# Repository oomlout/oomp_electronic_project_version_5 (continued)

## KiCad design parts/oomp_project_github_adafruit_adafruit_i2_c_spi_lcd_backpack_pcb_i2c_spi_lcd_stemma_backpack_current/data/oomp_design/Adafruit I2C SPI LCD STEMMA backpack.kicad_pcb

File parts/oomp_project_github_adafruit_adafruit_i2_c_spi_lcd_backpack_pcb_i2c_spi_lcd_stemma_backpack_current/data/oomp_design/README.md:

# OOMP KiCad design copy

Open `Adafruit I2C SPI LCD STEMMA backpack.kicad_pro` (or the `.kicad_pcb` / `.kicad_sch`) in KiCad. Local OOMP libraries are under `libraries/`. Original inputs are preserved in [../original/](../original/).

Only verified unchanged installed KiCad defaults were renamed. Modified, custom, unmatched and unavailable items remain unchanged. Soldering variants are never swapped during conversion. Existing pad coordinates, nets and UUIDs are preserved.

See [conversion_report.yaml](conversion_report.yaml) for every conversion and skip. Copy this directory before editing; regeneration refuses to overwrite edited design files.

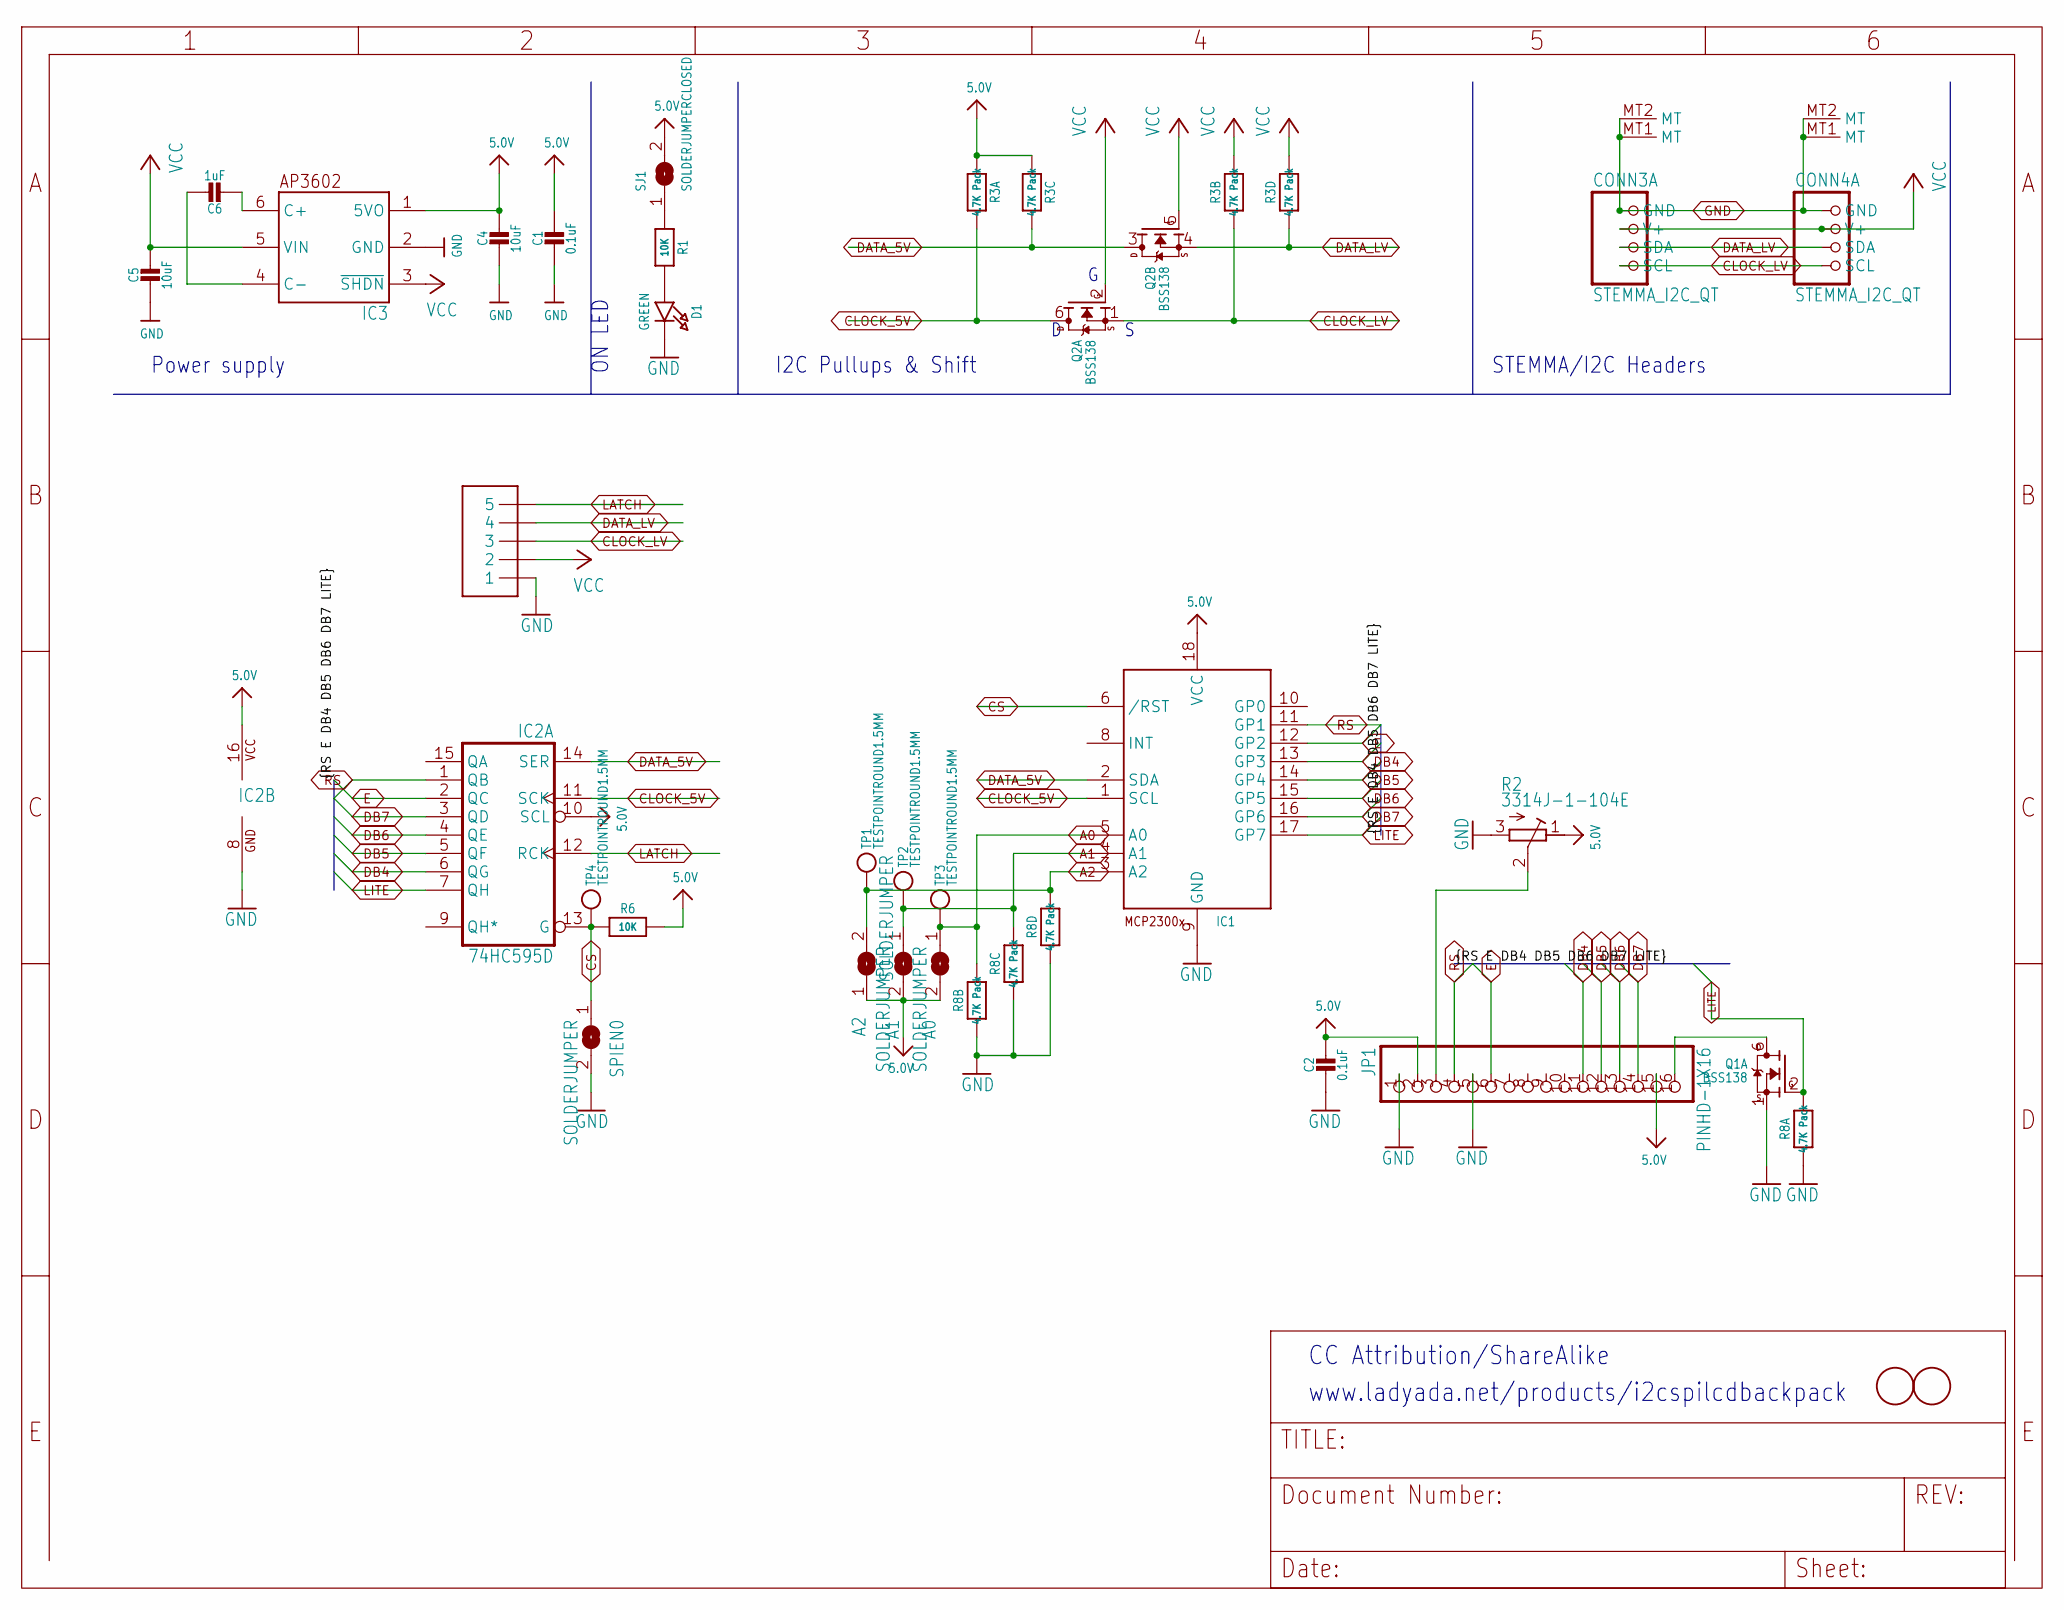
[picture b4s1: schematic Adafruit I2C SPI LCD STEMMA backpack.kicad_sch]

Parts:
A0, A1, A2: SOLDERJUMPER; SOLDERJUMPER_ARROW_NOPASTE
C1, C2: 0.1uF; 0603-NO
C4, C5: 10uF; 0805-NO
C6: 1uF; 0805-NO
CONN3, CONN4: STEMMA_I2C_QT; JST_SH4; LCSC C2845363
D1: GREEN; CHIPLED_0603_NOOUTLINE
IC1: MCP23008/SO; SO18W
IC2: 74HC595D; SO16
IC3: AP3602/RT9361; SOT23-6
J1: 1X5; 1X05-3.5MM
JP1: PINHD-1X16; 1X16
Q1, Q2: BSS138; SOT363; JLC_ROTATION 270
R1, R6: 10K; 0603-NO
R2: 3314J-1-104E; RTRIM3314J
R3, R8: 4.7K Pack; RESPACK_4X0603
SJ1: SOLDERJUMPERCLOSED; SOLDERJUMPER_CLOSEDWIRE
SPIEN0: SOLDERJUMPER; SOLDERJUMPER_ARROW_NOPASTE
TP1, TP2, TP3, TP4: TESTPOINTROUND1.5MM; TESTPOINT_ROUND_1.5MM
U$1, U$2: FIDUCIAL; FIDUCIAL_1MM

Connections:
5.0V: A0.2, A1.2, A2.1, C1.1, C2.1, C4.1, IC1.18 (VCC), IC2.10 (SCL), IC2.16 (VCC), IC3.1 (5VO), JP1.2, JP1.15, R2.1 (E), R3.1, R3.3 (1), R6.1, SJ1.2
A0: A0.1, IC1.5 (A0), R8.7 (2), TP3.P$1
A1: A1.1, IC1.4 (A1), R8.6 (2), TP2.P$1
A2: A2.2, IC1.3 (A2), R8.5 (2), TP1.P$1
CLOCK_5V: IC1.1 (SCL), IC2.11 (SCK), Q2.6 (D), R3.8 (2)
CLOCK_LV: CONN3.4 (SCL), CONN4.4 (SCL), J1.3, Q2.1 (S), R3.7 (2)
CONTRAST: JP1.3, R2.2 (S)
CS: IC1.6 (/RST), IC2.13 (G), R6.2, SPIEN0.1, TP4.P$1
DATA_5V: IC1.2 (SDA), IC2.14 (SER), Q2.3 (D), R3.6 (2)
DATA_LV: CONN3.3 (SDA), CONN4.3 (SDA), J1.4, Q2.4 (S), R3.5 (2)
DB4: IC1.13 (GP3), IC2.6 (QG), JP1.11
DB5: IC1.14 (GP4), IC2.5 (QF), JP1.12
DB6: IC1.15 (GP5), IC2.4 (QE), JP1.13
DB7: IC1.16 (GP6), IC2.3 (QD), JP1.14
E: IC1.12 (GP2), IC2.2 (QC), JP1.6
GND: C1.2, C2.2, C4.2, C5.2, CONN3.1 (GND), CONN3.MT1 (MT), CONN3.MT2 (MT), CONN4.1 (GND), CONN4.MT1 (MT), CONN4.MT2 (MT), D1.C, IC1.9 (GND), IC2.8 (GND), IC3.2 (GND), J1.1, JP1.1, JP1.5, Q1.1 (S), R2.3 (A), R8.1, R8.2 (1), R8.3 (1), R8.4 (1), SPIEN0.2
LATCH: IC2.12 (RCK), J1.5
LEDK: JP1.16, Q1.6 (D)
LITE: IC1.17 (GP7), IC2.7 (QH), Q1.2 (G), R8.8 (2)
unnamed: D1.A, R1.2
unnamed: R1.1, SJ1.1
unnamed: C6.2, IC3.6 (C+)
unnamed: C6.1, IC3.4 (C-)
RS: IC1.11 (GP1), IC2.1 (QB), JP1.4
VCC: C5.1, CONN3.2 (V+), CONN4.2 (V+), IC3.3 (~SHDN), IC3.5 (VIN), J1.2, Q2.2 (G), Q2.5 (G), R3.2 (1), R3.4 (1)

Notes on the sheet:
I2C Pullups & Shift
Power supply
CC Attribution/ShareAlike
www.ladyada.net/products/i2cspilcdbackpack
STEMMA/I2C Headers
ON LED

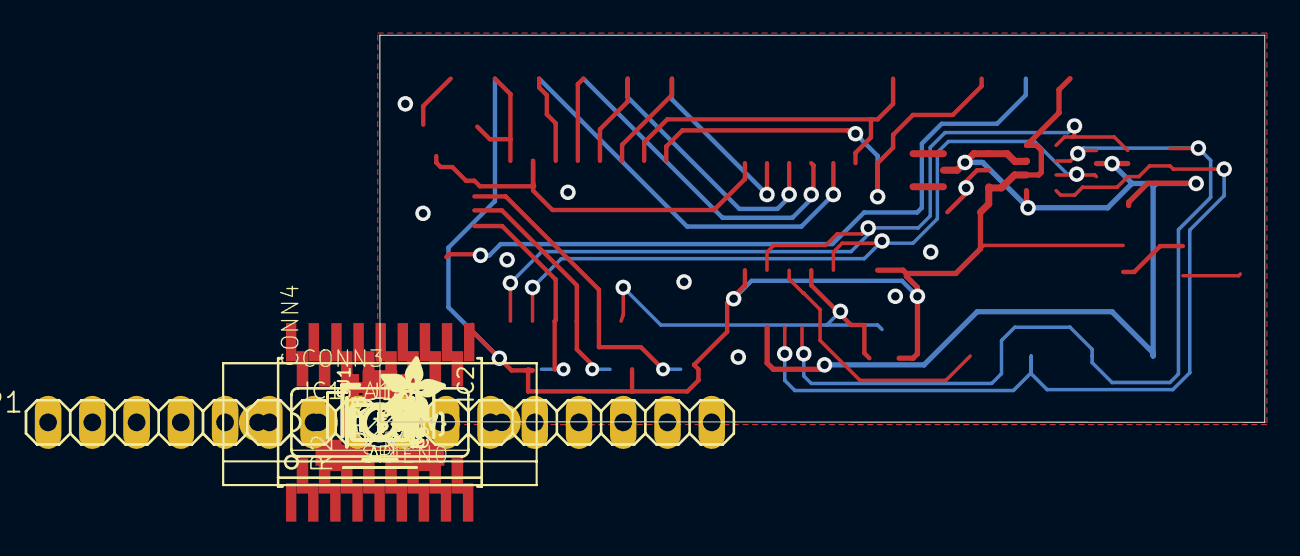
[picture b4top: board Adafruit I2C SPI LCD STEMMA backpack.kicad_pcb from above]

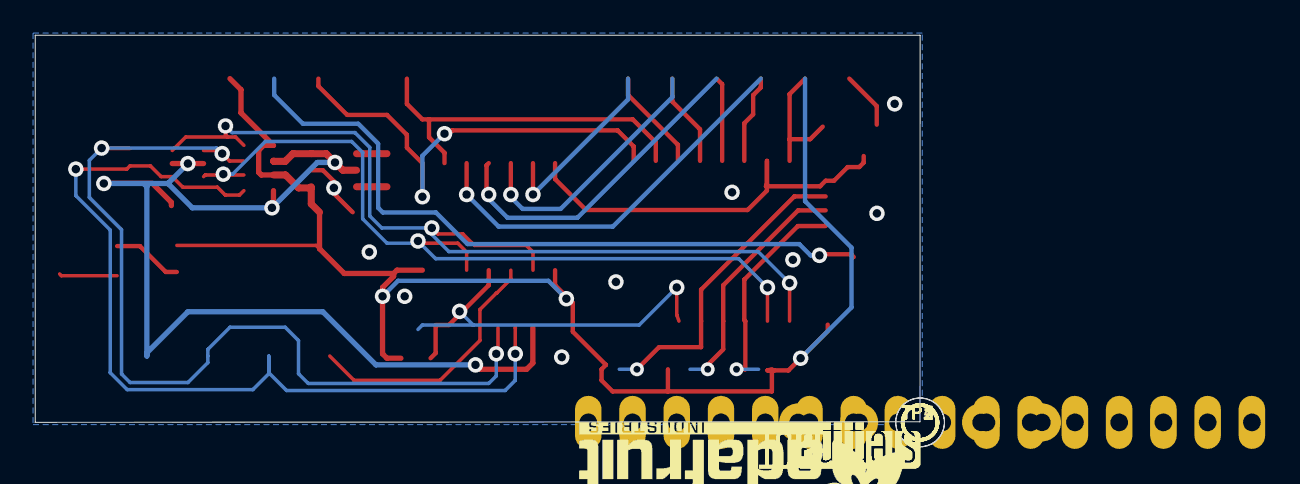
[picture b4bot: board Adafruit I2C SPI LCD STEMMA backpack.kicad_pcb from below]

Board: 16 copper layers, 50.8 x 22.2 mm, 51 parts (8 on the bottom side), 25 nets.

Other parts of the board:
PLABEL0: PLABEL0
PLABEL1: PLABEL1
PLABEL2: PLABEL2
PLABEL3: PLABEL3
PLABEL4: PLABEL4
PLABEL5: PLABEL5
PLABEL6: PLABEL6
PLABEL7: PLABEL7
PLABEL8: PLABEL8
PLABEL9: PLABEL9
PLABEL10: PLABEL10
PLABEL11: PLABEL11
PLABEL12: PLABEL12
U$4: ADAFRUIT_3.5MM
U$7: PCBFEAT-REV-040
U$11, U$12: STEMMAQT
U$23: ADAFRUIT_TEXT_20MM
UNK_HOLE_0: dummyfp0
UNK_HOLE_1: dummyfp1

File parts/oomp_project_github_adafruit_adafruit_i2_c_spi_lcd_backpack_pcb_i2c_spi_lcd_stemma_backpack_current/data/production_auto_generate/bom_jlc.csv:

Comment,Designator,Footprint,LCSC Part #
,JP1,Adafruit I2C SPI LCD STEMMA backpack-import-fps:1X16,C7501270
,U$4,Adafruit I2C SPI LCD STEMMA backpack-import-fps:ADAFRUIT_3.5MM,
,U$23,Adafruit I2C SPI LCD STEMMA backpack-import-fps:ADAFRUIT_TEXT_20MM,
,U$7,Adafruit I2C SPI LCD STEMMA backpack-import-fps:PCBFEAT-REV-040,
,PLABEL0,Adafruit I2C SPI LCD STEMMA backpack-import-fps:PLABEL0,
,PLABEL1,Adafruit I2C SPI LCD STEMMA backpack-import-fps:PLABEL1,
,PLABEL10,Adafruit I2C SPI LCD STEMMA backpack-import-fps:PLABEL10,
,PLABEL11,Adafruit I2C SPI LCD STEMMA backpack-import-fps:PLABEL11,
,PLABEL12,Adafruit I2C SPI LCD STEMMA backpack-import-fps:PLABEL12,
,PLABEL2,Adafruit I2C SPI LCD STEMMA backpack-import-fps:PLABEL2,
,PLABEL3,Adafruit I2C SPI LCD STEMMA backpack-import-fps:PLABEL3,
,PLABEL4,Adafruit I2C SPI LCD STEMMA backpack-import-fps:PLABEL4,
,PLABEL5,Adafruit I2C SPI LCD STEMMA backpack-import-fps:PLABEL5,
,PLABEL6,Adafruit I2C SPI LCD STEMMA backpack-import-fps:PLABEL6,
,PLABEL7,Adafruit I2C SPI LCD STEMMA backpack-import-fps:PLABEL7,
,PLABEL8,Adafruit I2C SPI LCD STEMMA backpack-import-fps:PLABEL8,
,PLABEL9,Adafruit I2C SPI LCD STEMMA backpack-import-fps:PLABEL9,
,"A0,A1,A2,SPIEN0",Adafruit I2C SPI LCD STEMMA backpack-import-fps:SOLDERJUMPER_ARROW_NOPASTE,
,"U$11,U$12",Adafruit I2C SPI LCD STEMMA backpack-import-fps:STEMMAQT,
,"TP1,TP2,TP3,TP4",Adafruit I2C SPI LCD STEMMA backpack-import-fps:TESTPOINT_ROUND_1.5MM,
0.1uF,"C1,C2",Adafruit I2C SPI LCD STEMMA backpack-import-fps:0603-NO,C14663
10K,"R1,R6",Adafruit I2C SPI LCD STEMMA backpack-import-fps:0603-NO,C98220
10uF,"C4,C5",Adafruit I2C SPI LCD STEMMA backpack-import-fps:0805-NO,
1uF,C6,Adafruit I2C SPI LCD STEMMA backpack-import-fps:0805-NO,
1X5,J1,Adafruit I2C SPI LCD STEMMA backpack-import-fps:1X05-3.5MM,C42431835
3314J-1-104E,R2,Adafruit I2C SPI LCD STEMMA backpack-import-fps:RTRIM3314J,
4.7K Pack,"R3,R8",Adafruit I2C SPI LCD STEMMA backpack-import-fps:RESPACK_4X0603,C23162
74HC595D,IC2,Adafruit I2C SPI LCD STEMMA backpack-import-fps:SO16,
AP3602/RT9361,IC3,Adafruit I2C SPI LCD STEMMA backpack-import-fps:SOT23-6,
BSS138,"Q1,Q2",Adafruit I2C SPI LCD STEMMA backpack-import-fps:SOT363,
FIDUCIAL,"U$1,U$2",Adafruit I2C SPI LCD STEMMA backpack-import-fps:FIDUCIAL_1MM,
GREEN,D1,Adafruit I2C SPI LCD STEMMA backpack-import-fps:CHIPLED_0603_NOOUTLINE,
MCP23008/SO,IC1,Adafruit I2C SPI LCD STEMMA backpack-import-fps:SO18W,
STEMMA_I2C_QT,"CONN3,CONN4",Adafruit I2C SPI LCD STEMMA backpack-import-fps:JST_SH4,C160404

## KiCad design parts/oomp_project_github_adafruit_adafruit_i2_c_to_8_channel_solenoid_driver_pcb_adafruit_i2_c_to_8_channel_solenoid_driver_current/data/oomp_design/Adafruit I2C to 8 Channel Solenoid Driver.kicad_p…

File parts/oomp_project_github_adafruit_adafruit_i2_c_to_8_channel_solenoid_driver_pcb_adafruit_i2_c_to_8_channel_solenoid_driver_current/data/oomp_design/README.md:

# OOMP KiCad design copy

Open `Adafruit I2C to 8 Channel Solenoid Driver.kicad_pro` (or the `.kicad_pcb` / `.kicad_sch`) in KiCad. Local OOMP libraries are under `libraries/`. Original inputs are preserved in [../original/](../original/).

Only verified unchanged installed KiCad defaults were renamed. Modified, custom, unmatched and unavailable items remain unchanged. Soldering variants are never swapped during conversion. Existing pad coordinates, nets and UUIDs are preserved.

See [conversion_report.yaml](conversion_report.yaml) for every conversion and skip. Copy this directory before editing; regeneration refuses to overwrite edited design files.

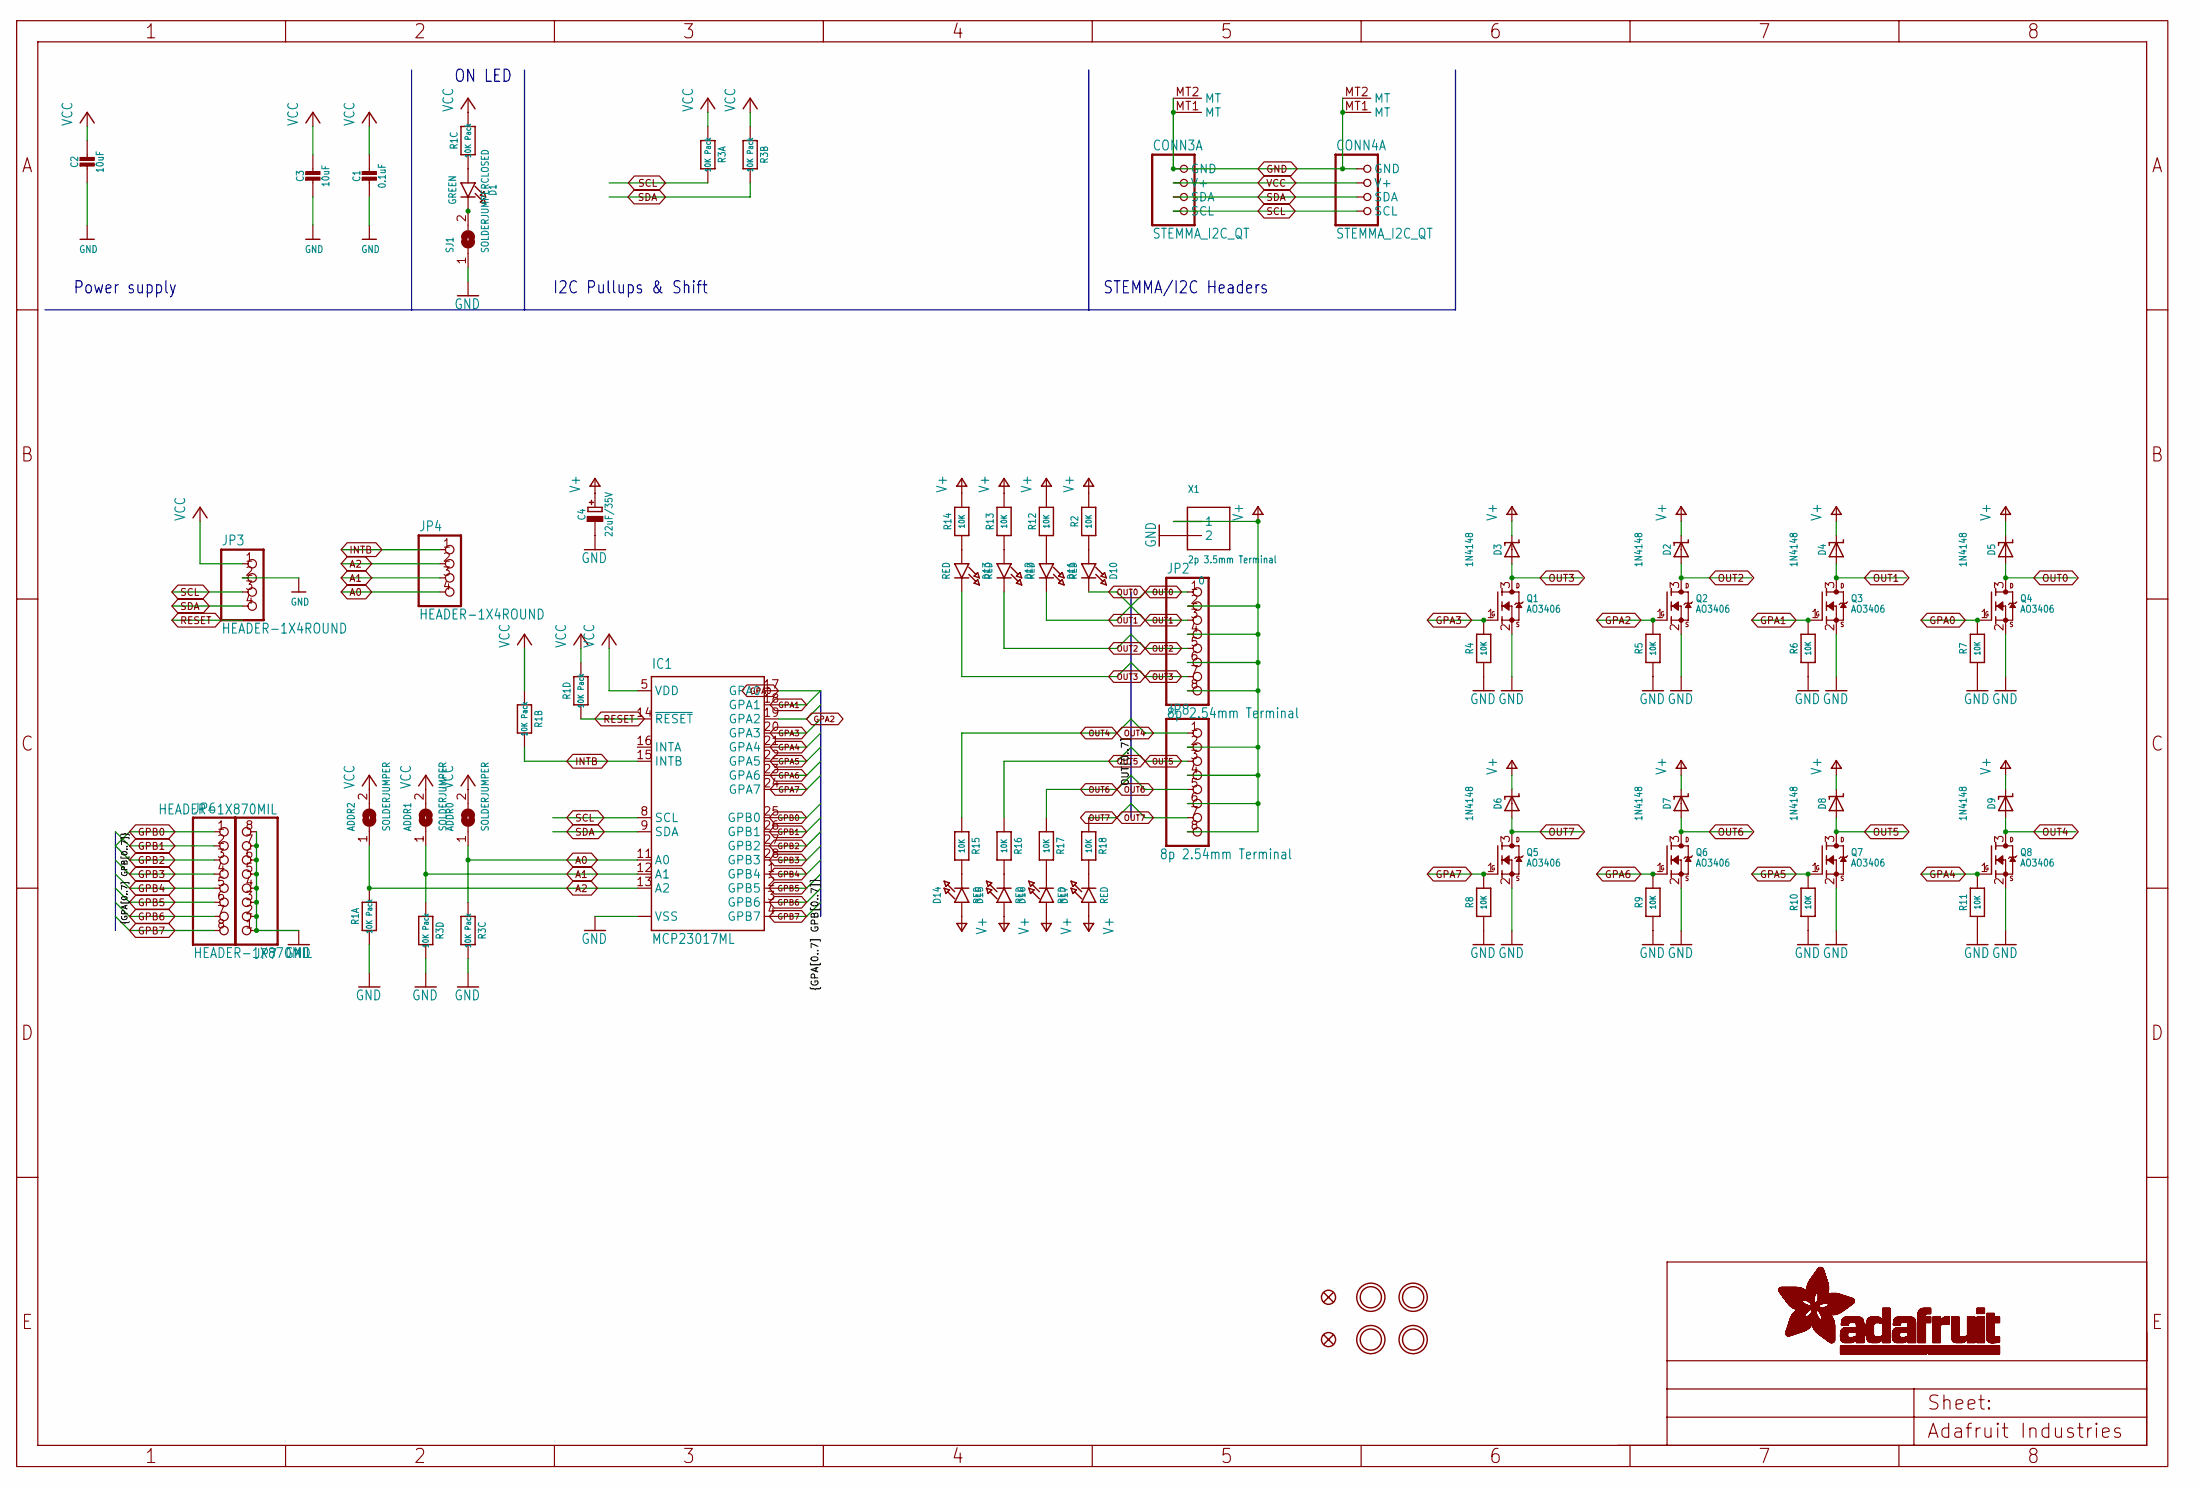
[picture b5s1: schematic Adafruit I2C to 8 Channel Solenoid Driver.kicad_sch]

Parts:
ADDR0, ADDR1, ADDR2: SOLDERJUMPER; SOLDERJUMPER_ARROW_NOPASTE
C1: 0.1uF; 0603-NO
C2, C3: 10uF; 0805-NO
C4: 22uF/35V; PANASONIC_C
CONN3, CONN4: STEMMA_I2C_QT; JST_SH4; LCSC C2845363
D1: GREEN; CHIPLED_0603_NOOUTLINE
D2, D3, D4, D5, D6, D7, D8, D9: 1N4148; SOD-323
D10, D11, D12, D13, D14, D15, D16, D17: RED; CHIPLED_0603_NOOUTLINE
FID3, FID4: FIDUCIAL_1MM
IC1: MCP23017ML; QFN28-ML_6X6MM; MPN MCP23017-E/ML
JP2, JP8: 8p 2.54mm Terminal; 1X08_2.54MMTERMINAL
JP3, JP4: HEADER-1X4ROUND; 1X04_ROUND
JP6, JP7: HEADER-1X870MIL; 1X08_ROUND_70
Q1, Q2, Q3, Q4, Q5, Q6, Q7, Q8: AO3406; SOT23-WIDE
R1, R3: 10K Pack; RESPACK_4X0603
R2, R4, R5, R6, R7, R8, R9, R10, R11, R12, R13, R14, R15, R16, R17, R18: 10K; 0603-NO
SJ1: SOLDERJUMPERCLOSED; SOLDERJUMPER_CLOSEDWIRE
U$1, U$17, U$19, U$21: MOUNTINGHOLE2.5; MOUNTINGHOLE_2.5_PLATED
X1: 2p 3.5mm Terminal; TERMBLOCK_1X2-3.5MM

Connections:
A0: ADDR0.1, IC1.11 (A0), JP4.4, R3.3 (1)
A1: ADDR1.1, IC1.12 (A1), JP4.3, R3.4 (1)
A2: ADDR2.1, IC1.13 (A2), JP4.2, R1.8 (2)
GND: C1.2, C2.2, C3.2, C4.-, CONN3.1 (GND), CONN3.MT1 (MT), CONN3.MT2 (MT), CONN4.1 (GND), CONN4.MT1 (MT), CONN4.MT2 (MT), IC1.6 (VSS), IC1.EXP (VSS), JP3.2, JP7.1, JP7.2, JP7.3, JP7.4, JP7.5, JP7.6, JP7.7, JP7.8, Q1.2 (S), Q2.2 (S), Q3.2 (S), Q4.2 (S), Q5.2 (S), Q6.2 (S), Q7.2 (S), Q8.2 (S), R1.1, R3.5 (2), R3.6 (2), R4.1, R5.1, R6.1, R7.1, R8.1, R9.1, R10.1, R11.1, SJ1.1, X1.2
GPA0: IC1.17 (GPA0), Q4.1 (G), R7.2
GPA1: IC1.18 (GPA1), Q3.1 (G), R6.2
GPA2: IC1.19 (GPA2), Q2.1 (G), R5.2
GPA3: IC1.20 (GPA3), Q1.1 (G), R4.2
GPA4: IC1.21 (GPA4), Q8.1 (G), R11.2
GPA5: IC1.22 (GPA5), Q7.1 (G), R10.2
GPA6: IC1.23 (GPA6), Q6.1 (G), R9.2
GPA7: IC1.24 (GPA7), Q5.1 (G), R8.2
GPB0: IC1.25 (GPB0), JP6.1
GPB1: IC1.26 (GPB1), JP6.2
GPB2: IC1.27 (GPB2), JP6.3
GPB3: IC1.28 (GPB3), JP6.4
GPB4: IC1.1 (GPB4), JP6.5
GPB5: IC1.2 (GPB5), JP6.6
GPB6: IC1.3 (GPB6), JP6.7
GPB7: IC1.4 (GPB7), JP6.8
INTB: IC1.15 (INTB), JP4.1, R1.7 (2)
unnamed: D1.A, R1.3 (1)
unnamed: D1.C, SJ1.2
unnamed: D10.A, R2.1
unnamed: D11.A, R12.1
unnamed: D12.A, R13.1
unnamed: D13.A, R14.1
unnamed: D14.C, R15.2
unnamed: D15.C, R16.2
unnamed: D16.C, R17.2
unnamed: D17.C, R18.2
OUT0: D5.A, D10.C, JP2.1, Q4.3 (D)
OUT1: D4.A, D11.C, JP2.3, Q3.3 (D)
OUT2: D2.A, D12.C, JP2.5, Q2.3 (D)
OUT3: D3.A, D13.C, JP2.7, Q1.3 (D)
OUT4: D9.A, JP8.1, Q8.3 (D), R15.1
OUT5: D8.A, JP8.3, Q7.3 (D), R16.1
OUT6: D7.A, JP8.5, Q6.3 (D), R17.1
OUT7: D6.A, JP8.7, Q5.3 (D), R18.1
RESET: IC1.14 (~RESET), R1.4 (1)
SCL: CONN3.4 (SCL), CONN4.4 (SCL), IC1.8 (SCL), JP3.3, R3.8 (2)
SDA: CONN3.3 (SDA), CONN4.3 (SDA), IC1.9 (SDA), JP3.4, R3.7 (2)
V+: C4.+, D2.C, D3.C, D4.C, D5.C, D6.C, D7.C, D8.C, D9.C, D14.A, D15.A, D16.A, D17.A, JP2.2, JP2.4, JP2.6, JP2.8, JP8.2, JP8.4, JP8.6, JP8.8, R2.2, R12.2, R13.2, R14.2, X1.1
VCC: ADDR0.2, ADDR1.2, ADDR2.2, C1.1, C2.1, C3.1, CONN3.2 (V+), CONN4.2 (V+), IC1.5 (VDD), JP3.1, R1.2 (1), R1.5 (2), R1.6 (2), R3.1, R3.2 (1)

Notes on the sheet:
STEMMA/I2C Headers
ON LED
I2C Pullups & Shift
Power supply

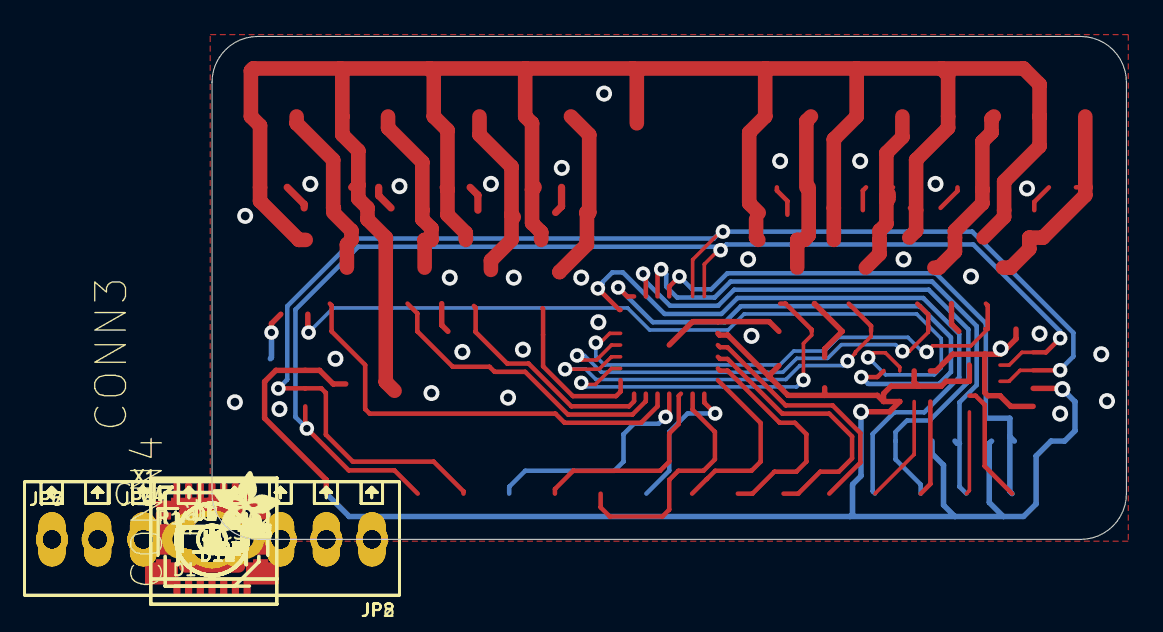
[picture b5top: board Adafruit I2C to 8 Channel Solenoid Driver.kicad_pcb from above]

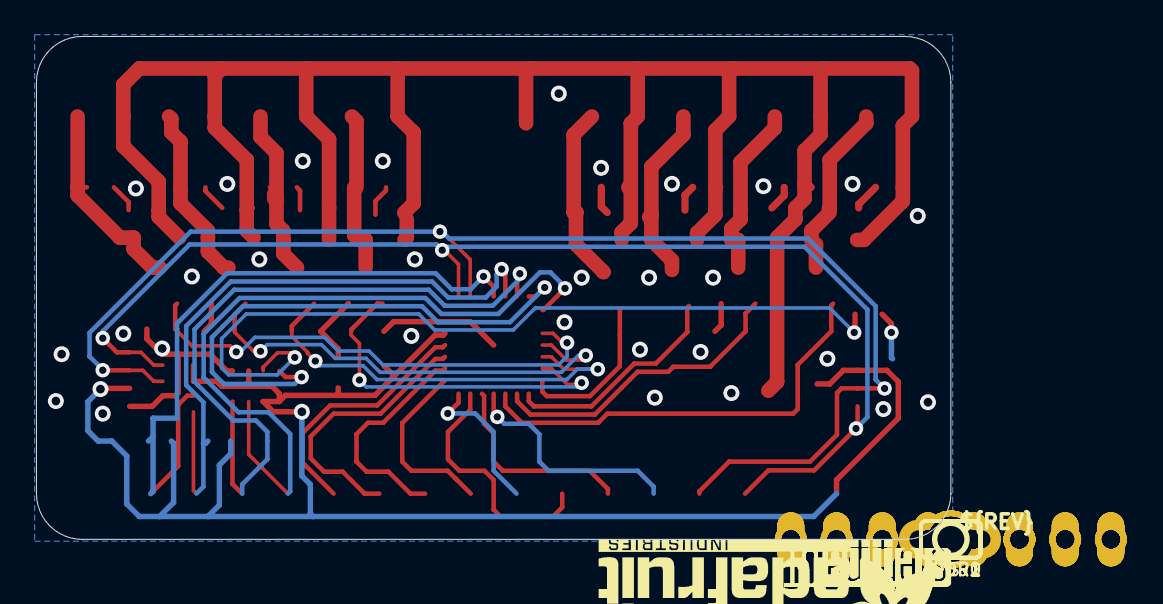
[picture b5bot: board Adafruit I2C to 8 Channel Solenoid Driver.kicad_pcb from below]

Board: 2 copper layers, 50.8 x 27.9 mm, 135 parts (32 on the bottom side), 44 nets.

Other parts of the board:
PLABEL0: PLABEL0
PLABEL1: PLABEL1
PLABEL2: PLABEL2
PLABEL3: PLABEL3
PLABEL4: PLABEL4
PLABEL5: PLABEL5
PLABEL6: PLABEL6
PLABEL7: PLABEL7
PLABEL8: PLABEL8
PLABEL9: PLABEL9
PLABEL10: PLABEL10
PLABEL11: PLABEL11
PLABEL12: PLABEL12
PLABEL13: PLABEL13
PLABEL14: PLABEL14
PLABEL15: PLABEL15
PLABEL16: PLABEL16
PLABEL17: PLABEL17
PLABEL18: PLABEL18
PLABEL19: PLABEL19
PLABEL20: PLABEL20
PLABEL21: PLABEL21
PLABEL22: PLABEL22
PLABEL23: PLABEL23
PLABEL24: PLABEL24
PLABEL25: PLABEL25
PLABEL26: PLABEL26
PLABEL27: PLABEL27
PLABEL28: PLABEL28
PLABEL29: PLABEL29
PLABEL30: PLABEL30
PLABEL31: PLABEL31
PLABEL32: PLABEL32
PLABEL33: PLABEL33
PLABEL34: PLABEL34
PLABEL35: PLABEL35
PLABEL36: PLABEL36
PLABEL37: PLABEL37
PLABEL38: PLABEL38
PLABEL39: PLABEL39
PLABEL40: PLABEL40
PLABEL41: PLABEL41
PLABEL42: PLABEL42
PLABEL43: PLABEL43
PLABEL44: PLABEL44
PLABEL45: PLABEL45
PLABEL46: PLABEL46
PLABEL47: PLABEL47
PLABEL48: PLABEL48
PLABEL49: PLABEL49
PLABEL50: PLABEL50
PLABEL51: PLABEL51
PLABEL52: PLABEL52
PLABEL53: PLABEL53
PLABEL54: PLABEL54
PLABEL55: PLABEL55
PLABEL56: PLABEL56
PLABEL57: PLABEL57
PLABEL58: PLABEL58
PLABEL59: PLABEL59
PLABEL60: PLABEL60
U$2: PLUS; SYMBOL_PLUS
U$3: SYMBOL_MINUS
U$4: ADAFRUIT_3.5MM
U$7: ADAFRUIT_TEXT_20MM
U$25: PCBFEAT-REV-040
U$30, U$31: STEMMAQT

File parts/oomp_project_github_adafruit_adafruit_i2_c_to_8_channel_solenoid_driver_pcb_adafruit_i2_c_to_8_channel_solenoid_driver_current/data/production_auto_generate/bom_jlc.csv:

Comment,Designator,Footprint,LCSC Part #
,"JP3,JP4",Adafruit I2C to 8 Channel Solenoid Driver-import-fps:1X04_ROUND,C42431795
,"JP6,JP7",Adafruit I2C to 8 Channel Solenoid Driver-import-fps:1X08_ROUND_70,C492421
,U$4,Adafruit I2C to 8 Channel Solenoid Driver-import-fps:ADAFRUIT_3.5MM,
,U$7,Adafruit I2C to 8 Channel Solenoid Driver-import-fps:ADAFRUIT_TEXT_20MM,
,U$25,Adafruit I2C to 8 Channel Solenoid Driver-import-fps:PCBFEAT-REV-040,
,PLABEL0,Adafruit I2C to 8 Channel Solenoid Driver-import-fps:PLABEL0,
,PLABEL1,Adafruit I2C to 8 Channel Solenoid Driver-import-fps:PLABEL1,
,PLABEL10,Adafruit I2C to 8 Channel Solenoid Driver-import-fps:PLABEL10,
,PLABEL11,Adafruit I2C to 8 Channel Solenoid Driver-import-fps:PLABEL11,
,PLABEL12,Adafruit I2C to 8 Channel Solenoid Driver-import-fps:PLABEL12,
,PLABEL13,Adafruit I2C to 8 Channel Solenoid Driver-import-fps:PLABEL13,
,PLABEL14,Adafruit I2C to 8 Channel Solenoid Driver-import-fps:PLABEL14,
,PLABEL15,Adafruit I2C to 8 Channel Solenoid Driver-import-fps:PLABEL15,
,PLABEL16,Adafruit I2C to 8 Channel Solenoid Driver-import-fps:PLABEL16,
,PLABEL17,Adafruit I2C to 8 Channel Solenoid Driver-import-fps:PLABEL17,
,PLABEL18,Adafruit I2C to 8 Channel Solenoid Driver-import-fps:PLABEL18,
,PLABEL19,Adafruit I2C to 8 Channel Solenoid Driver-import-fps:PLABEL19,
,PLABEL2,Adafruit I2C to 8 Channel Solenoid Driver-import-fps:PLABEL2,
,PLABEL20,Adafruit I2C to 8 Channel Solenoid Driver-import-fps:PLABEL20,
,PLABEL21,Adafruit I2C to 8 Channel Solenoid Driver-import-fps:PLABEL21,
,PLABEL22,Adafruit I2C to 8 Channel Solenoid Driver-import-fps:PLABEL22,
,PLABEL23,Adafruit I2C to 8 Channel Solenoid Driver-import-fps:PLABEL23,
,PLABEL24,Adafruit I2C to 8 Channel Solenoid Driver-import-fps:PLABEL24,
,PLABEL25,Adafruit I2C to 8 Channel Solenoid Driver-import-fps:PLABEL25,
,PLABEL26,Adafruit I2C to 8 Channel Solenoid Driver-import-fps:PLABEL26,
,PLABEL27,Adafruit I2C to 8 Channel Solenoid Driver-import-fps:PLABEL27,
,PLABEL28,Adafruit I2C to 8 Channel Solenoid Driver-import-fps:PLABEL28,
,PLABEL29,Adafruit I2C to 8 Channel Solenoid Driver-import-fps:PLABEL29,
,PLABEL3,Adafruit I2C to 8 Channel Solenoid Driver-import-fps:PLABEL3,
,PLABEL30,Adafruit I2C to 8 Channel Solenoid Driver-import-fps:PLABEL30,
,PLABEL31,Adafruit I2C to 8 Channel Solenoid Driver-import-fps:PLABEL31,
,PLABEL32,Adafruit I2C to 8 Channel Solenoid Driver-import-fps:PLABEL32,
,PLABEL33,Adafruit I2C to 8 Channel Solenoid Driver-import-fps:PLABEL33,
,PLABEL34,Adafruit I2C to 8 Channel Solenoid Driver-import-fps:PLABEL34,
,PLABEL35,Adafruit I2C to 8 Channel Solenoid Driver-import-fps:PLABEL35,
,PLABEL36,Adafruit I2C to 8 Channel Solenoid Driver-import-fps:PLABEL36,
,PLABEL37,Adafruit I2C to 8 Channel Solenoid Driver-import-fps:PLABEL37,
,PLABEL38,Adafruit I2C to 8 Channel Solenoid Driver-import-fps:PLABEL38,
,PLABEL39,Adafruit I2C to 8 Channel Solenoid Driver-import-fps:PLABEL39,
,PLABEL4,Adafruit I2C to 8 Channel Solenoid Driver-import-fps:PLABEL4,
,PLABEL40,Adafruit I2C to 8 Channel Solenoid Driver-import-fps:PLABEL40,
,PLABEL41,Adafruit I2C to 8 Channel Solenoid Driver-import-fps:PLABEL41,
,PLABEL42,Adafruit I2C to 8 Channel Solenoid Driver-import-fps:PLABEL42,
,PLABEL43,Adafruit I2C to 8 Channel Solenoid Driver-import-fps:PLABEL43,
,PLABEL44,Adafruit I2C to 8 Channel Solenoid Driver-import-fps:PLABEL44,
,PLABEL45,Adafruit I2C to 8 Channel Solenoid Driver-import-fps:PLABEL45,
,PLABEL46,Adafruit I2C to 8 Channel Solenoid Driver-import-fps:PLABEL46,
,PLABEL47,Adafruit I2C to 8 Channel Solenoid Driver-import-fps:PLABEL47,
,PLABEL48,Adafruit I2C to 8 Channel Solenoid Driver-import-fps:PLABEL48,
,PLABEL49,Adafruit I2C to 8 Channel Solenoid Driver-import-fps:PLABEL49,
,PLABEL5,Adafruit I2C to 8 Channel Solenoid Driver-import-fps:PLABEL5,
,PLABEL50,Adafruit I2C to 8 Channel Solenoid Driver-import-fps:PLABEL50,
,PLABEL51,Adafruit I2C to 8 Channel Solenoid Driver-import-fps:PLABEL51,
,PLABEL52,Adafruit I2C to 8 Channel Solenoid Driver-import-fps:PLABEL52,
,PLABEL53,Adafruit I2C to 8 Channel Solenoid Driver-import-fps:PLABEL53,
,PLABEL54,Adafruit I2C to 8 Channel Solenoid Driver-import-fps:PLABEL54,
,PLABEL55,Adafruit I2C to 8 Channel Solenoid Driver-import-fps:PLABEL55,
,PLABEL56,Adafruit I2C to 8 Channel Solenoid Driver-import-fps:PLABEL56,
,PLABEL57,Adafruit I2C to 8 Channel Solenoid Driver-import-fps:PLABEL57,
,PLABEL58,Adafruit I2C to 8 Channel Solenoid Driver-import-fps:PLABEL58,
,PLABEL59,Adafruit I2C to 8 Channel Solenoid Driver-import-fps:PLABEL59,
,PLABEL6,Adafruit I2C to 8 Channel Solenoid Driver-import-fps:PLABEL6,
,PLABEL60,Adafruit I2C to 8 Channel Solenoid Driver-import-fps:PLABEL60,
,PLABEL7,Adafruit I2C to 8 Channel Solenoid Driver-import-fps:PLABEL7,
,PLABEL8,Adafruit I2C to 8 Channel Solenoid Driver-import-fps:PLABEL8,
,PLABEL9,Adafruit I2C to 8 Channel Solenoid Driver-import-fps:PLABEL9,
,"ADDR0,ADDR1,ADDR2",Adafruit I2C to 8 Channel Solenoid Driver-import-fps:SOLDERJUMPER_ARROW_NOPASTE,
,"U$30,U$31",Adafruit I2C to 8 Channel Solenoid Driver-import-fps:STEMMAQT,
,U$3,Adafruit I2C to 8 Channel Solenoid Driver-import-fps:SYMBOL_MINUS,
0.1uF,C1,Adafruit I2C to 8 Channel Solenoid Driver-import-fps:0603-NO,C14663
10K,"R2,R4,R5,R6,R7,R8,R9,R10,R11,R12,R13,R14,R15,R16,R17,R18",Adafruit I2C to 8 Channel Solenoid Driver-import-fps:0603-NO,C98220
10K Pack,"R1,R3",Adafruit I2C to 8 Channel Solenoid Driver-import-fps:RESPACK_4X0603,C98220
10uF,"C2,C3",Adafruit I2C to 8 Channel Solenoid Driver-import-fps:0805-NO,
1N4148,"D2,D3,D4,D5,D6,D7,D8,D9",Adafruit I2C to 8 Channel Solenoid Driver-import-fps:SOD-323,
22uF/35V,C4,Adafruit I2C to 8 Channel Solenoid Driver-import-fps:PANASONIC_C,
2p 3.5mm Terminal,X1,Adafruit I2C to 8 Channel Solenoid Driver-import-fps:TERMBLOCK_1X2-3.5MM,
8p 2.54mm Terminal,"JP2,JP8",Adafruit I2C to 8 Channel Solenoid Driver-import-fps:1X08_2.54MMTERMINAL,C492421
AO3406,"Q1,Q2,Q3,Q4,Q5,Q6,Q7,Q8",Adafruit I2C to 8 Channel Solenoid Driver-import-fps:SOT23-WIDE,
GREEN,D1,Adafruit I2C to 8 Channel Solenoid Driver-import-fps:CHIPLED_0603_NOOUTLINE,
MCP23017ML,IC1,Adafruit I2C to 8 Channel Solenoid Driver-import-fps:QFN28-ML_6X6MM,
PLUS,U$2,Adafruit I2C to 8 Channel Solenoid Driver-import-fps:SYMBOL_PLUS,
RED,"D10,D11,D12,D13,D14,D15,D16,D17",Adafruit I2C to 8 Channel Solenoid Driver-import-fps:CHIPLED_0603_NOOUTLINE,
STEMMA_I2C_QT,"CONN3,CONN4",Adafruit I2C to 8 Channel Solenoid Driver-import-fps:JST_SH4,C160404

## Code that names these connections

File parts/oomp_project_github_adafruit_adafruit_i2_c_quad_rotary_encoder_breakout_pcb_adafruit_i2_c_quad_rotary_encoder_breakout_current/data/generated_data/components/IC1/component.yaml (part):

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    dnp: false
    pins:
    - number: '1'
      name: PA02/RX/MISO/SCL/AIN2
      electrical_type: bidirectional
      graphic_style: line
      local_position:
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        pin_number: P$B
        pin_name: P$B
    - number: '2'
      name: PA03/SCK/TA.3/AIN3
      electrical_type: bidirectional
      graphic_style: line
      local_position:
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        pin_number: '2'
        pin_name: '2'
    - number: '5'
      name: PA04/TA.4/TD.A/Y0/AIN4
      electrical_type: bidirectional
      graphic_style: line
      local_position:
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      no_connect: false
      connected_to: []
    - number: '6'
      name: PA05/TA.5/TB/TD.B/Y1/AIN5
      electrical_type: bidirectional
      graphic_style: line
      local_position:
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        pin_number: '1'
        pin_name: '1'
    - number: '7'
      name: PA06/DAC/Y2/AIN6
      electrical_type: bidirectional
      graphic_style: line
      local_position:
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        pin_number: '1'
        pin_name: '1'
    - number: '8'
      name: PA07/Y3/AIN7
      electrical_type: bidirectional
      graphic_style: line
      local_position:
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        pin_number: '2'
        pin_name: '2'
    - number: '9'
      name: PB7
      electrical_type: bidirectional
      graphic_style: line
      local_position:
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        pin_number: P$A
        pin_name: P$A
    - number: '10'
      name: PB6
      electrical_type: bidirectional
      graphic_style: line
      local_position:
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        pin_number: P$B
        pin_name: P$B
    - number: '11'
      name: PB5/TA.2/AIN8
      electrical_type: bidirectional
      graphic_style: line
      local_position:
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        pin_number: P$B
        pin_name: P$B
    - number: '12'
      name: PB4/TA.1/AIN9
      electrical_type: bidirectional
      graphic_style: line
      local_position:
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      no_connect: false
      connected_to: []
    - number: '14'
      name: PB2/TX/TA.2
      electrical_type: bidirectional
      graphic_style: line
      local_position:
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        pin_number: P$1
        pin_name: P$1
    - number: '15'
      name: PB1/SDA/TA.1/Y4/AIN0
      electrical_type: bidirectional
      graphic_style: line
      local_position:
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        pin_number: '2'
        pin_name: '2'
    - number: '16'
      name: PB0/SCL/TA.0/Y5/AIN11
      electrical_type: bidirectional
      graphic_style: line
      local_position:
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        pin_number: '2'
        pin_name: '2'
    - number: '17'
      name: PC0/SCK/TB/TD.C
      electrical_type: bidirectional
      graphic_style: line
      local_position:
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        pin_number: P$1
        pin_name: P$1
    - number: '18'
      name: PC1/MISO/TD.D
      electrical_type: bidirectional
      graphic_style: line
      local_position:
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        pin_number: P$A
        pin_name: P$A
    - number: '19'
      name: PC2/MOSI
      electrical_type: bidirectional
      graphic_style: line
      local_position:
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        pin_number: P$1
        pin_name: P$1
    - number: '20'
      name: PC3/SS/TA.3
      electrical_type: bidirectional
      graphic_style: line
      local_position:
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        pin_number: P$A
        pin_name: P$A
    - number: '21'
      name: PC4/TA.4
      electrical_type: bidirectional
      graphic_style: line
      local_position:
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        pin_number: P$B
        pin_name: P$B
    - number: '22'
      name: PC5/TA.5
      electrical_type: bidirectional
      graphic_style: line
      local_position:
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        pin_number: P$1
        pin_name: P$1
    - number: '23'
      name: PA0/UPDI/~{RESET}
      electrical_type: bidirectional
      graphic_style: line
      local_position:
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        pin_number: '1'
        pin_name: '1'
    - number: '24'
      name: PA01/TX/MOSI/SDA/AIN1
      electrical_type: bidirectional
      graphic_style: line
      local_position:
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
